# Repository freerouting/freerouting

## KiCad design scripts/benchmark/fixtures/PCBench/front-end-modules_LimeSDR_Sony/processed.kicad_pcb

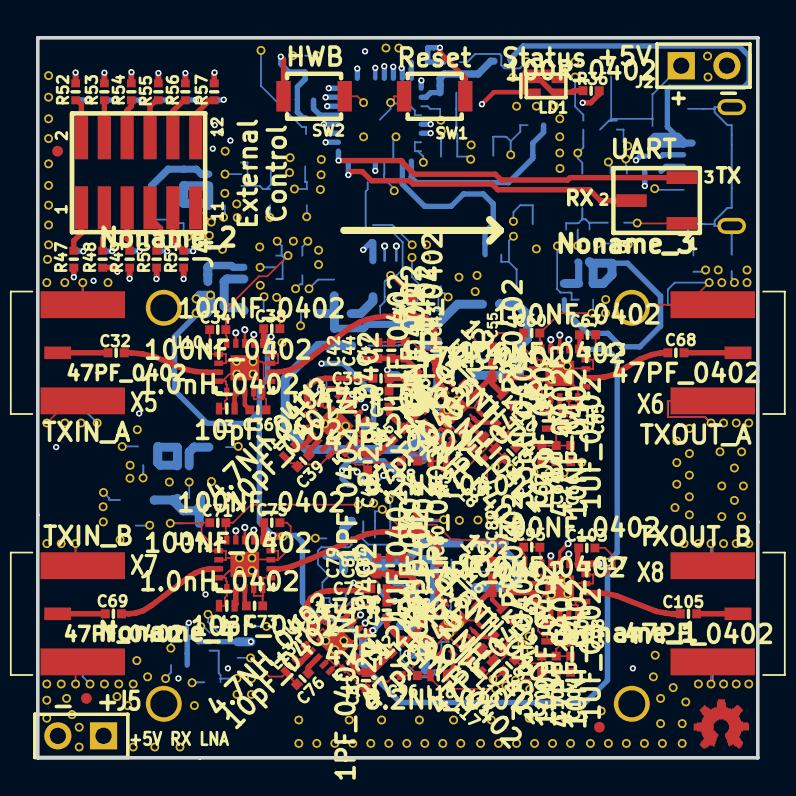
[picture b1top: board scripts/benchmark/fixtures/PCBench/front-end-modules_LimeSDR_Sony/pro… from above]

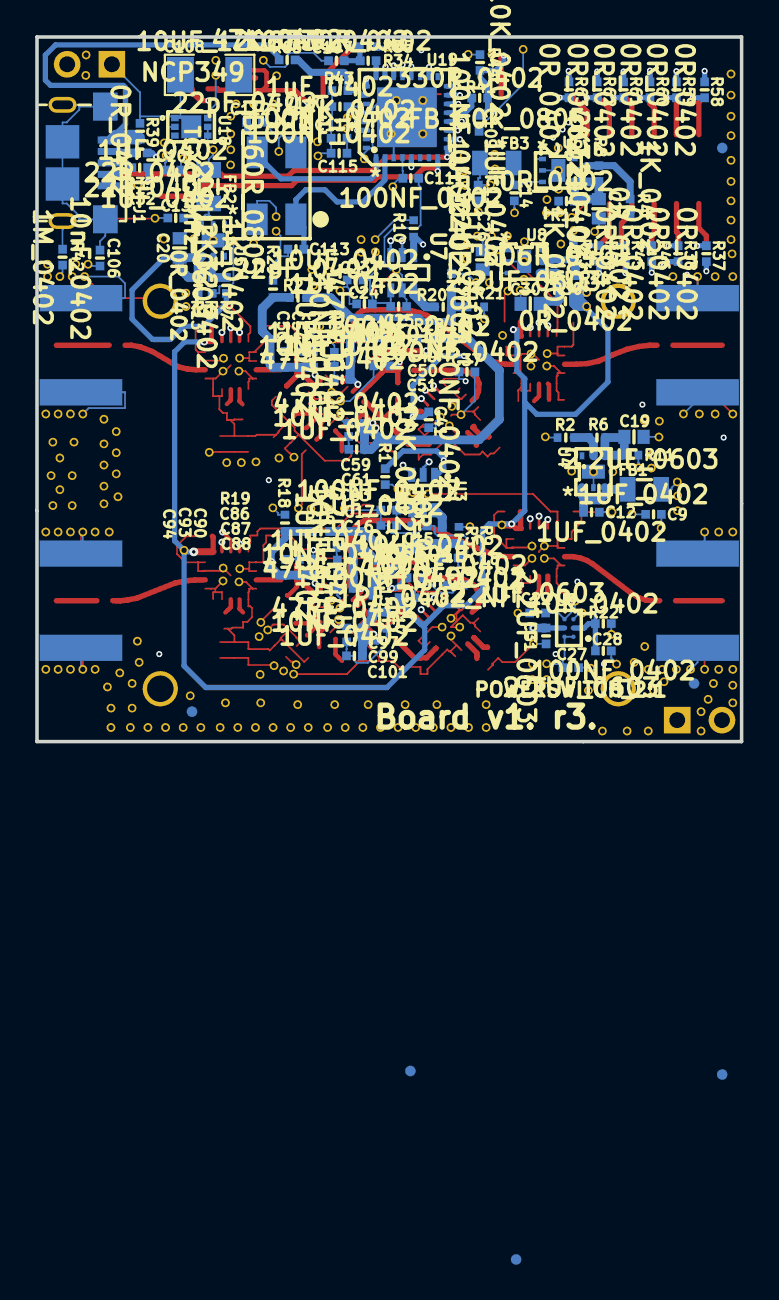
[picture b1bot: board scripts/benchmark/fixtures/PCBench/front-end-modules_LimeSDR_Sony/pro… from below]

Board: 6 copper layers, 40.0 x 40.0 mm, 529 parts (129 on the bottom side), 124 nets.

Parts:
ASTUB: VAL**; ASTUB
C9, C10, C11, C12, C13, C14, C16, C18, C24, C29, C42, C49, C56, C63, C66, C79, C86, C94, C101, C104: 1UF_0402; SMD0402
C15, C23: 10UF_0402; SMD0402
C17, C25, C28, C34, C37, C38, C41, C60, C67, C71, C74, C75, C78, C95, C103, C107, C109, C111, C114, C115: 100NF_0402; SMD0402
C19, C20, C21, C26, C30: 2.2UF_0603; SMD0603
C22, C27, C31: 2.2UF_0603; SMD0402
C32, C69: 47PF_0402; SM0402
C33, C46, C70, C83: 1PF_0402_NF; SMD0402
C35, C47, C51, C52, C53, C57, C58, C59, C62, C68, C72, C84, C88, C90, C91, C92, C96, C97, C100, C105: 47PF_0402; SMD0402
C36, C39, C43, C73, C76, C80: 10pF_0402; SMD0402
C40, C55, C77, C89: 1PF_0402; SMD0402
C44, C50, C54, C61, C64, C81, C87, C93, C99, C102: 10NF_0402; SMD0402
C45, C82: 47pF_0402; SMD0402
C48, C85: 2.2pF_0402; SMD0402
C65, C98: 100pF_0402; SMD0402
C106: 10nF_0402; SMD0402
C108: 10UF_1206; SMD1206
C110: 1uF_0402; SMD0402
C112, C113: 22pF_0402; SMD0402
FB1: FB_60R_0805; SM0805
FB2, FB3: FB_60R_0805; SMD0805
FD1, FD2, FD3, FD4, FD4_2, FD5, FD5_2, FD6, FD6_2: FIDUCIAL; Fiducial
GND_VIA: VAL**; GND_VIA
GND_VIA_2, GND_VIA_3, GND_VIA_4, GND_VIA_5, GND_VIA_6, GND_VIA_7, GND_VIA_8, GND_VIA_9, GND_VIA_10, GND_VIA_11, GND_VIA_12, GND_VIA_13, GND_VIA_14, GND_VIA_15, GND_VIA_16, GND_VIA_17, GND_VIA_18, GND_VIA_19, GND_VIA_20, GND_VIA_21, GND_VIA_22, GND_VIA_23, GND_VIA_24, GND_VIA_25, GND_VIA_26, GND_VIA_27, GND_VIA_28, GND_VIA_29, GND_VIA_30, GND_VIA_31, GND_VIA_32, GND_VIA_33, GND_VIA_34, GND_VIA_35, GND_VIA_36, GND_VIA_37, GND_VIA_38, GND_VIA_39, GND_VIA_40, GND_VIA_41, GND_VIA_42, GND_VIA_43, GND_VIA_44, GND_VIA_45, GND_VIA_46, GND_VIA_47, GND_VIA_48, GND_VIA_49, GND_VIA_50, GND_VIA_51, GND_VIA_52, GND_VIA_53, GND_VIA_54, GND_VIA_55, GND_VIA_56, GND_VIA_57, GND_VIA_58, GND_VIA_59, GND_VIA_60, GND_VIA_61, GND_VIA_62, GND_VIA_63, GND_VIA_64, GND_VIA_65, GND_VIA_66, GND_VIA_67, GND_VIA_68, GND_VIA_69, GND_VIA_70, GND_VIA_71, GND_VIA_72, GND_VIA_73, GND_VIA_74, GND_VIA_75, GND_VIA_76, GND_VIA_77, GND_VIA_78, GND_VIA_79, GND_VIA_80, GND_VIA_81, GND_VIA_82, GND_VIA_83, GND_VIA_84, GND_VIA_85, GND_VIA_86, GND_VIA_87, GND_VIA_88, GND_VIA_89, GND_VIA_90, GND_VIA_91, GND_VIA_92, GND_VIA_93, GND_VIA_94, GND_VIA_95, GND_VIA_96, GND_VIA_97, GND_VIA_98, GND_VIA_99, GND_VIA_100, GND_VIA_101, GND_VIA_102, GND_VIA_103, GND_VIA_104, GND_VIA_105, GND_VIA_106, GND_VIA_107, GND_VIA_108, GND_VIA_109, GND_VIA_110, GND_VIA_111, GND_VIA_112, GND_VIA_113, GND_VIA_114, GND_VIA_115, GND_VIA_116, GND_VIA_117, GND_VIA_118, GND_VIA_119, GND_VIA_120, GND_VIA_121, GND_VIA_122, GND_VIA_123, GND_VIA_124, GND_VIA_125, GND_VIA_126, GND_VIA_127, GND_VIA_128, GND_VIA_129, GND_VIA_130, GND_VIA_131, GND_VIA_132, GND_VIA_133, GND_VIA_134, GND_VIA_135, GND_VIA_136, GND_VIA_137, GND_VIA_138, GND_VIA_139, GND_VIA_140, GND_VIA_141, GND_VIA_142, GND_VIA_143, GND_VIA_144, GND_VIA_145, GND_VIA_146, GND_VIA_147, GND_VIA_148, GND_VIA_149, GND_VIA_150, GND_VIA_151, GND_VIA_152, GND_VIA_153, GND_VIA_154, GND_VIA_155, GND_VIA_156, GND_VIA_157, GND_VIA_158, GND_VIA_159, GND_VIA_160, GND_VIA_161, GND_VIA_162, GND_VIA_163, GND_VIA_164, GND_VIA_165, GND_VIA_166, GND_VIA_167, GND_VIA_168, GND_VIA_169, GND_VIA_170, GND_VIA_171, GND_VIA_172, GND_VIA_173, GND_VIA_174, GND_VIA_175, GND_VIA_176, GND_VIA_177, GND_VIA_178, GND_VIA_179, GND_VIA_180, GND_VIA_181, GND_VIA_182, GND_VIA_183, GND_VIA_184, GND_VIA_185, GND_VIA_186, GND_VIA_187, GND_VIA_188, GND_VIA_189, GND_VIA_190, GND_VIA_191, GND_VIA_192, GND_VIA_193, GND_VIA_194, GND_VIA_195, GND_VIA_196, GND_VIA_197, GND_VIA_198, GND_VIA_199, GND_VIA_200, GND_VIA_201, GND_VIA_202, GND_VIA_203, GND_VIA_204, GND_VIA_205, GND_VIA_206, GND_VIA_207, GND_VIA_208, GND_VIA_209, GND_VIA_210, GND_VIA_211, GND_VIA_212, GND_VIA_213, GND_VIA_214, GND_VIA_215, GND_VIA_216, GND_VIA_217, GND_VIA_218, GND_VIA_219, GND_VIA_220, GND_VIA_221, GND_VIA_222, GND_VIA_223, GND_VIA_224, GND_VIA_225, GND_VIA_226, GND_VIA_227, GND_VIA_228, GND_VIA_229, GND_VIA_230, GND_VIA_231, GND_VIA_232, GND_VIA_233, GND_VIA_234, GND_VIA_235, GND_VIA_236, GND_VIA_237, GND_VIA_238, GND_VIA_239, GND_VIA_240, GND_VIA_241, GND_VIA_242, GND_VIA_243, GND_VIA_244, GND_VIA_245, GND_VIA_246, GND_VIA_247, GND_VIA_248, GND_VIA_249, GND_VIA_250, GND_VIA_251, GND_VIA_252, GND_VIA_253, GND_VIA_254, GND_VIA_255, GND_VIA_256, GND_VIA_257, GND_VIA_258, GND_VIA_259, GND_VIA_260, GND_VIA_261, GND_VIA_262, GND_VIA_263, GND_VIA_264, GND_VIA_265, GND_VIA_266, GND_VIA_267, GND_VIA_268, GND_VIA_269, GND_VIA_270, GND_VIA_271, GND_VIA_272, GND_VIA_273, GND_VIA_274, GND_VIA_275, GND_VIA_276, GND_VIA_277, GND_VIA_278, GND_VIA_279, GND_VIA_280, GND_VIA_281, GND_VIA_282, GND_VIA_283, GND_VIA_284, GND_VIA_285, GND_VIA_286, GND_VIA_287, GND_VIA_288, GND_VIA_289, GND_VIA_290, GND_VIA_291, GND_VIA_292: VAL**; GND_VIA
J1: MICRO_USB2_B; microUSB2
J2: pinhead_2_NF; pinhead2
J3: PINHEADER_1X3_SM; Pinhead_1x3_SMD
J4: Pinheader_2x6_SMD_1.27; Pinhead_2x6_SMD
J5: pinhead_2; pinhead2
L3, L12: 1.0nH_0402; IND_0402
L4, L13: 4.7NH_0402; IND_0402
L5, L6, L10, L14, L15, L19: 12NH_0402; IND_0402
L7, L16: 22NH_0402; IND_0402
L8, L17: 5.6NH_0402; IND_0402
L9, L18: 8.2NH_0402; IND_0402
L11, L20: 3.3nH_0402; IND_0402
LD1: LED_0603_GR
Noname_1, Noname_2, Noname_3, Noname_4: mounting_via_2
R1, R22, R44: 10K_0402; SMD0402
R2, R6: 200R_0402; R_SM0402
R3, R4, R23: 1K_0402; SMD0402
R5, R13: 0R_0402; SM0402
R7, R8: 2K32_0402; SMD0402
R9, R21: 0R_0402_NF; R_SM0402
R10: 10K_0402; R_SM0402
R11, R20, R47, R48, R49, R50, R51, R52, R53, R54, R55, R56, R57: 0R_0402; R_SM0402
R12, R30, R37, R38, R39, R45, R46, R58, R59, R60, R61, R62, R63, R64: 0R_0402; SMD0402
R14, R15, R16, R25, R26, R27: 15K_0402; R_SM0402
R17, R18, R19, R28, R29, R31: 4K3_0402; R_SM0402
R24: 806R_0402; SMD0402
R32, R33: 22R_0402; SMD0402
R34, R41: 330R_0402; SMD0402
R35: 33K_0402; R_SM0402
R36: 100R_0402; SMD0402
R42: 1M_0402; SMD0402
R43, R65: 47K_0402; SMD0402
SW1, SW2: SW_Tactile; SW_B3U-1000P
U3, U7: AD5601B; SC-70-6
U4, U5, U6, U8: MIC37122YMT_ADJ_6TMLF; 6TMLF
U9: POWERSWITCH_2:1; 6-UFBGA
U10, U11, U13, U14, U15, U17: CXM3624UR; UQFN_18
U12, U16: CXGXXXX; 20PIN-VQFN
U18: NCP349; 6-DFN
U19: AT90USB162-16MUR; VQFN32
X5, X7: SMA_PLUG; SMA
X6, X8: SMA_edge; SMA
XT1: TCXO_8MHz; XO_4DFN
open harware: VAL**; OS_Logo

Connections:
+1.8V: C38.2, C41.2, C67.2, C75.2, C78.2, C103.2, GND_VIA_122.1, GND_VIA_123.1, GND_VIA_124.1, GND_VIA_125.1, GND_VIA_126.1, GND_VIA_127.1, R30.2, U10.14, U11.14, U13.14, U14.14, U15.14, U17.14
+2V: C22.1, GND_VIA_159.1, GND_VIA_160.1, GND_VIA_161.1, GND_VIA_162.1, GND_VIA_164.1, GND_VIA_165.1, R9.1, R11.2, R21.1, U9.C2
+3.3V: C15.1, C16.1, C17.1, C23.1, C24.1, C25.1, C26.1, C34.2, C37.2, C60.2, C71.2, C74.2, C95.2, GND_VIA_43.1, GND_VIA_44.1, GND_VIA_45.1, GND_VIA_46.1, GND_VIA_61.1, GND_VIA_62.1, GND_VIA_63.1, GND_VIA_64.1, GND_VIA_75.1, GND_VIA_97.1, GND_VIA_98.1, GND_VIA_99.1, GND_VIA_100.1, GND_VIA_101.1, GND_VIA_102.1, GND_VIA_134.1, GND_VIA_135.1, R1.1, R10.1, R13.2, U3.4, U7.4, U8.1, U8.3, U10.18, U11.18, U13.18, U14.18, U15.18, U17.18
+3.3V_uC: C110.1, C111.1, C114.1, C115.1, GND_VIA_103.1, GND_VIA_104.1, GND_VIA_105.1, GND_VIA_106.1, GND_VIA_107.1, GND_VIA_108.1, GND_VIA_109.1, GND_VIA_110.1, GND_VIA_111.1, GND_VIA_112.1, GND_VIA_113.1, R12.2, R35.2, R44.2, U19.4, U19.27, U19.31, U19.32
+5V: C9.1, C10.1, C11.1, C27.1, C53.2, C58.1, C62.1, C64.1, C66.1, C91.2, C96.1, C100.1, C102.1, C104.1, FB1.1, FB2.1, FB3.1, GND_VIA.1, GND_VIA_2.1, GND_VIA_29.1, GND_VIA_30.1, GND_VIA_31.1, GND_VIA_32.1, GND_VIA_33.1, GND_VIA_34.1, GND_VIA_35.1, GND_VIA_47.1, GND_VIA_48.1, GND_VIA_49.1, GND_VIA_50.1, GND_VIA_51.1, GND_VIA_52.1, GND_VIA_53.1, GND_VIA_54.1, GND_VIA_55.1, GND_VIA_56.1, GND_VIA_57.1, GND_VIA_58.1, GND_VIA_59.1, GND_VIA_60.1, GND_VIA_74.1, GND_VIA_76.1, GND_VIA_77.1, GND_VIA_78.1, GND_VIA_79.1, GND_VIA_114.1, GND_VIA_115.1, GND_VIA_116.1, GND_VIA_117.1, GND_VIA_118.1, GND_VIA_119.1, GND_VIA_120.1, GND_VIA_121.1, GND_VIA_128.1, GND_VIA_129.1, J5.1, L8.1, L9.1, L10.1, L17.1, L18.1, L19.1, U9.A1, U9.A2, U18.4, U18.5
/Microcontroller/DATA+: J1.3, R32.1
/Microcontroller/DATA-: J1.2, R33.1
/Microcontroller/LED_G: R36.1, U19.21
/Microcontroller/LED_R: LD1.2, LD1.3, U19.20
/Microcontroller/UART_RX: J3.2, U19.8
/Microcontroller/UART_TX: J3.3, U19.9
/Microcontroller/VBUS: J1.1, R39.2, R65.2
GND: C9.2, C10.2, C11.2, C12.2, C13.2, C14.2, C15.2, C16.2, C17.2, C18.2, C19.2, C20.2, C21.2, C22.2, C23.2, C24.2, C25.2, C26.2, C27.2, C28.2, C29.2, C30.2, C31.2, C33.2, C34.1, C36.2, C37.1, C38.1, C39.2, C40.2, C41.1, C42.2, C44.2, C46.2, C47.2, C49.2, C50.2, C51.2, C52.2, C53.1, C54.2, C55.2, C56.2, C58.2, C59.2, C60.1, C61.2, C62.2, C63.2, C64.2, C65.2, C66.2, C67.1, C70.2, C71.1, C73.2, C74.1, C75.1, C76.2, C77.2, C78.1, C79.2, C81.2, C83.2, C84.2, C86.2, C87.2, C88.2, C89.2, C90.2, C91.1, C93.2, C94.2, C95.1, C96.2, C97.2, C98.2, C99.2, C100.2, C101.2, C102.2, C103.1, C104.2, C106.2, C107.2, C108.2, C109.2, C110.2, C111.2, C112.1, C113.1, C114.2, C115.2, GND_VIA_3.1, GND_VIA_4.1, GND_VIA_5.1, GND_VIA_6.1, GND_VIA_7.1, GND_VIA_8.1, GND_VIA_9.1, GND_VIA_10.1, GND_VIA_11.1, GND_VIA_12.1, GND_VIA_13.1, GND_VIA_14.1, GND_VIA_15.1, GND_VIA_16.1, GND_VIA_17.1, GND_VIA_18.1, GND_VIA_19.1, GND_VIA_20.1, GND_VIA_21.1, GND_VIA_22.1, GND_VIA_23.1, GND_VIA_24.1, GND_VIA_25.1, GND_VIA_26.1, GND_VIA_27.1, GND_VIA_28.1, GND_VIA_36.1, GND_VIA_37.1, GND_VIA_38.1, GND_VIA_39.1, GND_VIA_40.1, GND_VIA_41.1, GND_VIA_42.1, GND_VIA_65.1, GND_VIA_66.1, GND_VIA_67.1, GND_VIA_68.1, GND_VIA_69.1, GND_VIA_70.1, GND_VIA_71.1, GND_VIA_72.1, GND_VIA_73.1, GND_VIA_80.1, GND_VIA_81.1, GND_VIA_82.1, GND_VIA_83.1, GND_VIA_84.1, GND_VIA_85.1, GND_VIA_86.1, GND_VIA_87.1, GND_VIA_88.1, GND_VIA_89.1, GND_VIA_90.1, GND_VIA_91.1, GND_VIA_92.1, GND_VIA_93.1, GND_VIA_94.1, GND_VIA_95.1, GND_VIA_96.1, GND_VIA_130.1, GND_VIA_131.1, GND_VIA_132.1, GND_VIA_133.1, GND_VIA_136.1, GND_VIA_137.1, GND_VIA_138.1, GND_VIA_139.1, GND_VIA_140.1, GND_VIA_141.1, GND_VIA_142.1, GND_VIA_143.1, GND_VIA_144.1, GND_VIA_145.1, GND_VIA_146.1, GND_VIA_147.1, GND_VIA_148.1, GND_VIA_149.1, GND_VIA_150.1, GND_VIA_151.1, GND_VIA_152.1, GND_VIA_153.1, GND_VIA_154.1, GND_VIA_155.1, GND_VIA_156.1, GND_VIA_157.1, GND_VIA_158.1, GND_VIA_163.1, GND_VIA_166.1, GND_VIA_167.1, GND_VIA_168.1, GND_VIA_169.1, GND_VIA_170.1, GND_VIA_171.1, GND_VIA_172.1, GND_VIA_173.1, GND_VIA_174.1, GND_VIA_175.1, GND_VIA_176.1, GND_VIA_177.1, GND_VIA_178.1, GND_VIA_179.1, GND_VIA_180.1, GND_VIA_181.1, GND_VIA_182.1, GND_VIA_183.1, GND_VIA_184.1, GND_VIA_185.1, GND_VIA_186.1, GND_VIA_187.1, GND_VIA_188.1, GND_VIA_189.1, GND_VIA_190.1, GND_VIA_191.1, GND_VIA_192.1, GND_VIA_193.1, GND_VIA_194.1, GND_VIA_195.1, GND_VIA_196.1, GND_VIA_197.1, GND_VIA_198.1, GND_VIA_199.1, GND_VIA_200.1, GND_VIA_201.1, GND_VIA_202.1, GND_VIA_203.1, GND_VIA_204.1, GND_VIA_205.1, GND_VIA_206.1, GND_VIA_207.1, GND_VIA_208.1, GND_VIA_209.1, GND_VIA_210.1, GND_VIA_211.1, GND_VIA_212.1, GND_VIA_213.1, GND_VIA_214.1, GND_VIA_215.1, GND_VIA_216.1, GND_VIA_217.1, GND_VIA_218.1, GND_VIA_219.1, GND_VIA_220.1, GND_VIA_221.1, GND_VIA_222.1, GND_VIA_223.1, GND_VIA_224.1, GND_VIA_225.1, GND_VIA_226.1, GND_VIA_227.1, GND_VIA_228.1, GND_VIA_229.1, GND_VIA_230.1, GND_VIA_231.1, GND_VIA_232.1, GND_VIA_233.1, GND_VIA_234.1, GND_VIA_235.1, GND_VIA_236.1, GND_VIA_237.1, GND_VIA_238.1, GND_VIA_239.1, GND_VIA_240.1, GND_VIA_241.1, GND_VIA_242.1, GND_VIA_243.1, GND_VIA_244.1, GND_VIA_245.1, GND_VIA_246.1, GND_VIA_247.1, GND_VIA_248.1, GND_VIA_249.1, GND_VIA_250.1, GND_VIA_251.1, GND_VIA_252.1, GND_VIA_253.1, GND_VIA_254.1, GND_VIA_255.1, GND_VIA_256.1, GND_VIA_257.1, GND_VIA_258.1, GND_VIA_259.1, GND_VIA_260.1, GND_VIA_261.1, GND_VIA_262.1, GND_VIA_263.1, GND_VIA_264.1, GND_VIA_265.1, GND_VIA_266.1, GND_VIA_267.1, GND_VIA_268.1, GND_VIA_269.1, GND_VIA_270.1, GND_VIA_271.1, GND_VIA_272.1, GND_VIA_273.1, GND_VIA_274.1, GND_VIA_275.1, GND_VIA_276.1, GND_VIA_277.1, GND_VIA_278.1, GND_VIA_279.1, GND_VIA_280.1, GND_VIA_281.1, GND_VIA_282.1, GND_VIA_283.1, GND_VIA_284.1, GND_VIA_285.1, GND_VIA_286.1, GND_VIA_287.1, GND_VIA_288.1, GND_VIA_289.1, GND_VIA_290.1, GND_VIA_291.1, GND_VIA_292.1, J1.5, J2.2, J3.1, J4.11, J5.2, L3.2, L4.2, L6.2, L7.2, L11.2, L12.2, L13.2, L15.2, L16.2, L20.2, Noname_1.1, Noname_2.1, Noname_3.1, Noname_4.1, R2.1, R3.1, R4.1, R17.2, R18.2, R19.2, R22.1, R23.1, R28.2, R29.2, R31.2, R42.2, R43.1, SW1.1, SW2.2, U3.5, U4.2, U4.7, U5.2, U5.7, U6.2, U6.7, U7.5, U8.2, U8.7, U9.C1, U10.1, U10.2, U10.4, U10.5, U10.8, U10.9, U10.10, U10.12, U10.13, U10.19, U11.1, U11.2, U11.4, U11.5, U11.8, U11.9, U11.10, U11.12, U11.13, U11.19, U12.2, U12.6, U12.7, U12.10, U12.11, U12.13, U12.19, U12.20, U12.21, U13.1, U13.2, U13.4, U13.5, U13.8, U13.9, U13.10, U13.12, U13.13, U13.19, U14.1, U14.2, U14.4, U14.5, U14.8, U14.9, U14.10, U14.12, U14.13, U14.19, U15.1, U15.2, U15.4, U15.5, U15.8, U15.9, U15.10, U15.12, U15.13, U15.19, U16.2, U16.6, U16.7, U16.10, U16.11, U16.13, U16.19, U16.20, U16.21, U17.1, U17.2, U17.4, U17.5, U17.8, U17.9, U17.10, U17.12, U17.13, U17.19, U18.2, U18.6, U19.3, U19.28, X5.2, X5.3, X5.4, X5.5, X6.2, X6.3, X6.4, X6.5, X7.2, X7.3, X7.4, X7.5, X8.2, X8.3, X8.4, X8.5, XT1.2, XT1.4
MCU_SPI_DACA_SS: R10.2, R46.2, R49.2, U7.1
MCU_SPI_DACB_SS: R1.2, R45.2, R50.2, U3.1
MCU_SPI_MOSI: R37.2, R47.2, U3.3, U7.3, U10.15, U11.15, U13.15, U14.15, U15.15, U17.15
MCU_SPI_SCLK: R38.2, R48.2, U3.2, U7.2, U10.16, U11.16, U13.16, U14.16, U15.16, U17.16
MCU_TunerA_IN_SS: R54.1, R60.1, U10.17
MCU_TunerA_MID_SS: R53.1, R59.1, U11.17
MCU_TunerA_OUT_SS: R52.1, R58.1, U13.17
MCU_TunerB_IN_SS: R57.1, R63.1, U14.17
MCU_TunerB_MID_SS: R56.1, R62.1, U15.17
MCU_TunerB_OUT_SS: R55.1, R61.1, U17.17
unnamed: C12.1, FB1.2, U4.1, U4.3
unnamed: C13.1, FB2.2, U5.1, U5.3
unnamed: C14.1, FB3.2, U6.1, U6.3
unnamed: C18.1, R5.2, R9.2, R14.1, R15.1, R16.1
unnamed: C19.1, R6.1, R11.1, U4.4
unnamed: C20.1, R7.2, R13.1, U5.4
unnamed: C21.1, R8.2, R12.1, U6.4
unnamed: C29.1, R20.2, R21.2, R25.1, R26.1, R27.1
unnamed: C30.1, R24.2, R30.1, U8.4
unnamed: C32.1, X5.1
unnamed: C32.2, U10.3
unnamed: C33.1, C35.2, C48.1, L5.1, U12.15
unnamed: C35.1, U11.3
unnamed: C36.1, U10.7
unnamed: C39.1, U11.7
unnamed: C40.1, C43.1, U10.11
unnamed: C43.2, U12.12
unnamed: C45.1, C46.1, U11.11
unnamed: C45.2, C48.2, U12.16
unnamed: C55.1, C57.2, L10.2, U12.8
unnamed: C57.1, U13.3
unnamed: C65.1, U13.7
unnamed: C68.1, U13.11
unnamed: C68.2, X6.1
unnamed: C69.1, X7.1
unnamed: C69.2, U14.3
unnamed: C70.1, C72.2, C85.1, L14.1, U16.15
unnamed: C72.1, U15.3
unnamed: C73.1, U14.7
unnamed: C76.1, U15.7
unnamed: C77.1, C80.1, U14.11
unnamed: C80.2, U16.12
unnamed: C82.1, C83.1, U15.11
unnamed: C82.2, C85.2, U16.16
unnamed: C89.1, C92.2, L19.2, U16.8
unnamed: C92.1, U17.3
unnamed: C98.1, U17.7
unnamed: C105.1, U17.11
unnamed: C105.2, X8.1
unnamed: C106.1, J1.6, R42.1
unnamed: C107.1, R34.2, R35.1, SW1.2
unnamed: C109.1, R41.1, R44.1, SW2.1
unnamed: C112.2, U19.1, XT1.3
unnamed: C113.2, U19.2, XT1.1
unnamed: J4.1, R47.1
unnamed: J4.2, R52.2
unnamed: J4.3, R48.1
unnamed: J4.4, R53.2
unnamed: J4.5, R49.1
unnamed: J4.6, R54.2
unnamed: J4.7, R50.1
unnamed: J4.8, R55.2
unnamed: J4.9, R51.1
unnamed: J4.10, R56.2
unnamed: J4.12, R57.2
unnamed: L3.1, U10.6
unnamed: L4.1, U11.6
unnamed: L6.1, U12.3
unnamed: L7.1, U12.5
unnamed: L8.2, U12.4
unnamed: L9.2, U12.1
unnamed: L11.1, U13.6
unnamed: L12.1, U14.6
unnamed: L13.1, U15.6
unnamed: L15.1, U16.3
unnamed: L16.1, U16.5
unnamed: L17.2, U16.4
unnamed: L18.2, U16.1
unnamed: L20.1, U17.6
unnamed: LD1.1, LD1.4, R36.2
unnamed: R2.2, R6.2, U4.5
unnamed: R3.2, R7.1, U5.5
unnamed: R4.2, R8.1, U6.5
unnamed: R5.1, U3.6
unnamed: R20.1, U7.6
unnamed: R23.2, R24.1, U8.5
unnamed: R32.2, U19.29
unnamed: R33.2, U19.30
unnamed: R34.1, U19.24
unnamed: R37.1, U19.16
unnamed: R38.1, U19.15
unnamed: R41.2, U19.13
unnamed: R43.2, R65.1, U19.26
unnamed: R45.1, U19.18
unnamed: R46.1, U19.14
unnamed: R58.2, U19.25
unnamed: R59.2, U19.23
unnamed: R60.2, U19.22
unnamed: R61.2, U19.12
unnamed: R62.2, U19.11
unnamed: R63.2, U19.10
unnamed: R64.2, U19.5
PWR: C108.1, J2.1, R39.1, U18.1
Vd_Drive_select: C28.1, R22.2, R51.2, R64.1, U9.B1
Vd_Driver: C31.1, C42.1, C44.1, C47.1, C79.1, C81.1, C84.1, L5.2, L14.2, U9.B2
Vg1_2_A: C59.1, C61.1, C63.1, R26.2, R28.1, U12.17, U12.18
Vg1_2_B: C97.1, C99.1, C101.1, R15.2, R17.1, U16.17, U16.18
Vg3_A: C52.1, C54.1, C56.1, R27.2, R29.1, U12.9
Vg3_B: C90.1, C93.1, C94.1, R16.2, R18.1, U16.9
Vg_Driver_A: C49.1, C50.1, C51.1, R25.2, R31.1, U12.14
Vg_Driver_B: C86.1, C87.1, C88.1, R14.2, R19.1, U16.14

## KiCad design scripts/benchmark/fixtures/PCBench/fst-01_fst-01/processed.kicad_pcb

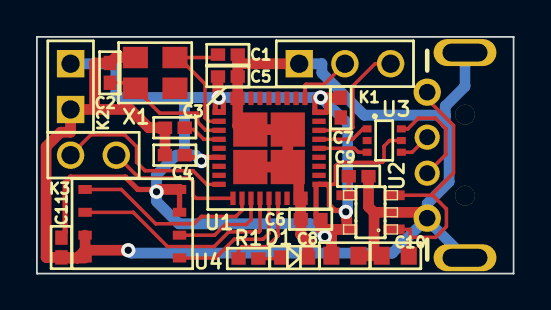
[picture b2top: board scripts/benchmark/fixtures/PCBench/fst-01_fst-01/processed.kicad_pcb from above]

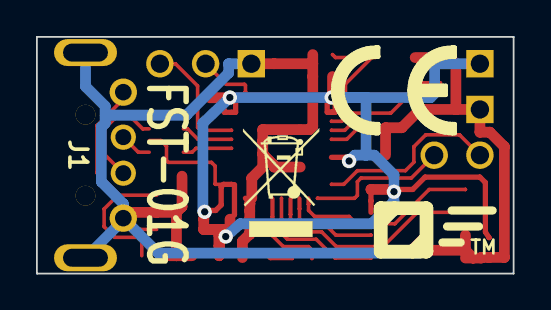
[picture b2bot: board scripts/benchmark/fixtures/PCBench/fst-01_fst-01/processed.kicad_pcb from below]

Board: 2 copper layers, 26.5 x 13.1 mm, 24 parts (2 on the bottom side), 21 nets.

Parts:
C1, C2: 27pF; c_0402
C3, C4, C5, C6, C7, C11: 0.1uF; c_0402
C8, C10: 4.7uF; c_0603
C9: 0.01uF; c_0402
CE_mark: Symbol_CE_SilkScreen_5mm
D1: LED; LED0603
FST-LOGO: VAL**; FST-LOGO
J1: USB_A; USB-A-PLUG
K1: CONN_3; SIL-3-2
K2: CONN_2; SIL-2-0
K3: CONN_2; SIL-2-2
R1: 510; r_0402
U1: STM32F103TB; QFN36
U2: LP2985-33DBVR; SOT23-5
U3: NUF2221W1; SOT363
U4: SST25VF032B; WSON8
X1: 12MHz; ABM8G

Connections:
+3V3: C4.2, C5.2, C6.2, C7.2, C8.1, C11.2, K2.1, U1.1, U1.6, U1.19, U1.27, U2.5, U3.5, U4.7, U4.8
/CLK: U1.12, U4.6
/D+: U1.24, U3.1
/D+_PLUG: J1.3, U3.6
/D-: U1.23, U3.3
/D-_PLUG: J1.2, U3.4
/LED: R1.2, U1.15
/MISO: U1.13, U4.2
/MOSI: U1.14, U4.5
/NRST: C3.1, U1.4
/NSS: U1.11, U4.1
/OSC_IN: C1.1, U1.2, X1.1
/OSC_OUT: C2.1, U1.3, X1.2
/PA2: K3.1, U1.9
/PA3: K3.2, U1.10
/SWCLK: K1.2, U1.28
/SWDIO: K1.3, U1.25
/VBUS: C10.1, J1.1, U2.1, U2.3
GND: C1.2, C2.2, C3.2, C4.1, C5.1, C6.1, C8.2, C9.2, C10.2, C11.1, D1.1, J1.4, J1.5, K1.1, K2.2, U1.17, U1.18, U1.35, U1.36, U2.2, U4.3, U4.4, X1.3
unnamed: C9.1, U2.4
unnamed: D1.2, R1.1

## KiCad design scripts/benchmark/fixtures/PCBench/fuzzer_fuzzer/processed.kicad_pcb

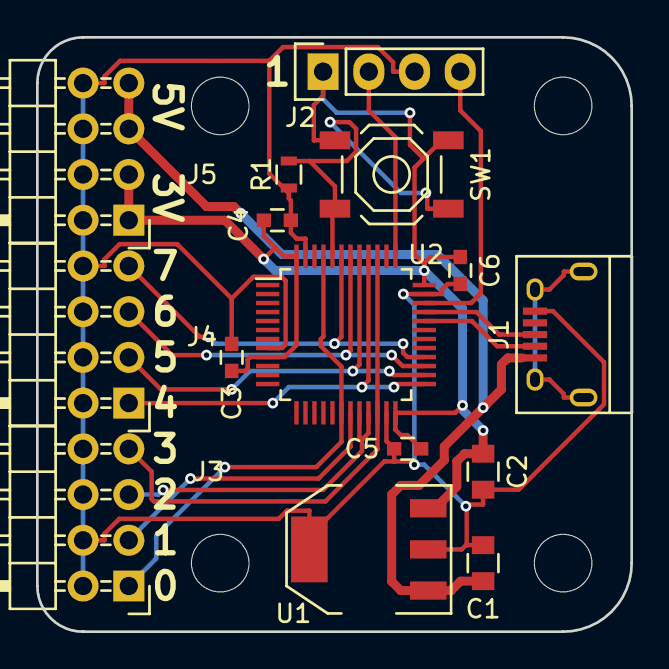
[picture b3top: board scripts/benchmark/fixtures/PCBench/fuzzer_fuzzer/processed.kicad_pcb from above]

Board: 2 copper layers, 33.0 x 33.0 mm, 15 parts (0 on the bottom side), 16 nets.

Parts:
C1, C2: 1u; C_0805
C3, C4, C5, C6: 100n; C_0603
J1: USB_OTG; USB_Micro-B
J2: CONN_01X04; Pin_Header_Straight_1x04
J3, J4, J5: CONN_02X04; Pin_Header_Angled_2x04
R1: 10K; R_0603
SW1: SPST; SW_SPST_TL3342
U1: SOT223-REG; SOT-223
U2: STM32F042-48; LQFP-48_7x7mm_Pitch0.5mm

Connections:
+5V: C1.1, J1.1, J5.5, J5.7, U1.1
/BOOT: R1.1, SW1.1, U2.44
/D0: J3.1, U2.18, U2.45
/D1: J3.3, U2.19
/D2: J3.5, U2.20, U2.21
/D3: J3.7, U2.22, U2.39
/D4: J4.1, U2.25, U2.40
/D5: J4.3, U2.26, U2.41
/D6: J4.5, U2.27, U2.42
/D7: J4.7, U2.28, U2.43
/SWCLK: J2.2, U2.37
/SWDAT: J2.4, U2.34
/USB_DM: J1.2, U2.32
/USB_DP: J1.3, U2.33
GND: C1.2, C2.2, C3.2, C4.2, C5.2, C6.2, J1.5, J2.3, J3.2, J3.4, J3.6, J3.8, J4.2, J4.4, J4.6, J4.8, J5.2, J5.4, J5.6, J5.8, R1.2, U1.2, U1.4, U2.8, U2.23, U2.35, U2.47
VDD: C2.1, C3.1, C4.1, C5.1, C6.1, J2.1, J5.1, J5.3, SW1.2, U1.3, U2.9, U2.24, U2.36, U2.48

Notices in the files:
scripts/benchmark/fixtures/PCBench/front-end-modules_LimeSDR_Sony/processed.kicad_pcb:
Copyright 2016 Lime Microsystems, Ltd.
WORK IS COVERED UNDER A CREATIVE COMMONS LICENSE (CC BY 3.0)
